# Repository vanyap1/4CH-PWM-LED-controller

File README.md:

# Потужний 4-канальний контролер освітлення

Контролер призначений для керування чотирма незалежними каналами освітлення за допомогою ШІМ. Підходить для амбіентного підсвічування та роботи з різними сенсорами присутності й освітленості.

## Основні можливості
- Керування **4 незалежними каналами**
- Регулювання яскравості через **ШІМ**
- Інтеграція з зовнішніми сенсорами:
  - Доплерівські сенсори присутності
  - PIR сенсори руху
  - Датчики освітленості
  - Інші сумісні датчики

## Система захисту
- **Температурний контроль** силових транзисторів
- Підтримка **зовнішнього NTC** біля навантаження
- **Захист по струму**
- **Контроль вхідної напруги** з блокуванням роботи в небезпечних діапазонах

## Технічні характеристики
- **Напруга живлення:** 12–26 В  
- **Споживання контролера:** ≤ 50 mA  
- **Максимальний струм комутації:**
  - до **12 А на канал**, або
  - до **12 А сумарно**

## Індикація роботи

### Зелений індикатор
- **Світиться** — нормальна робота  
- **Блимає** — перехідні процеси (зміна режиму, встановлення нового ШІМ)  
- **Вимкнений** — нештатна ситуація

### Червоний індикатор
- **Блимає** — відновлювані критичні стани  
  (критична напруга, перегрів, обмеження по струму, таймер блокування).  
  Виходи **вимкнені**  
- **Світиться** — фатальна помилка  
  (критичний перегрів, неможливість контролювати/відключити навантаження).  
  Скидання після перезапуску, якщо проблема не повторюється

## Програмування сценаріїв
Поведінку контролера, сценарії роботи та інтеграцію з сенсорами можна налаштовувати індивідуально під проєкт.

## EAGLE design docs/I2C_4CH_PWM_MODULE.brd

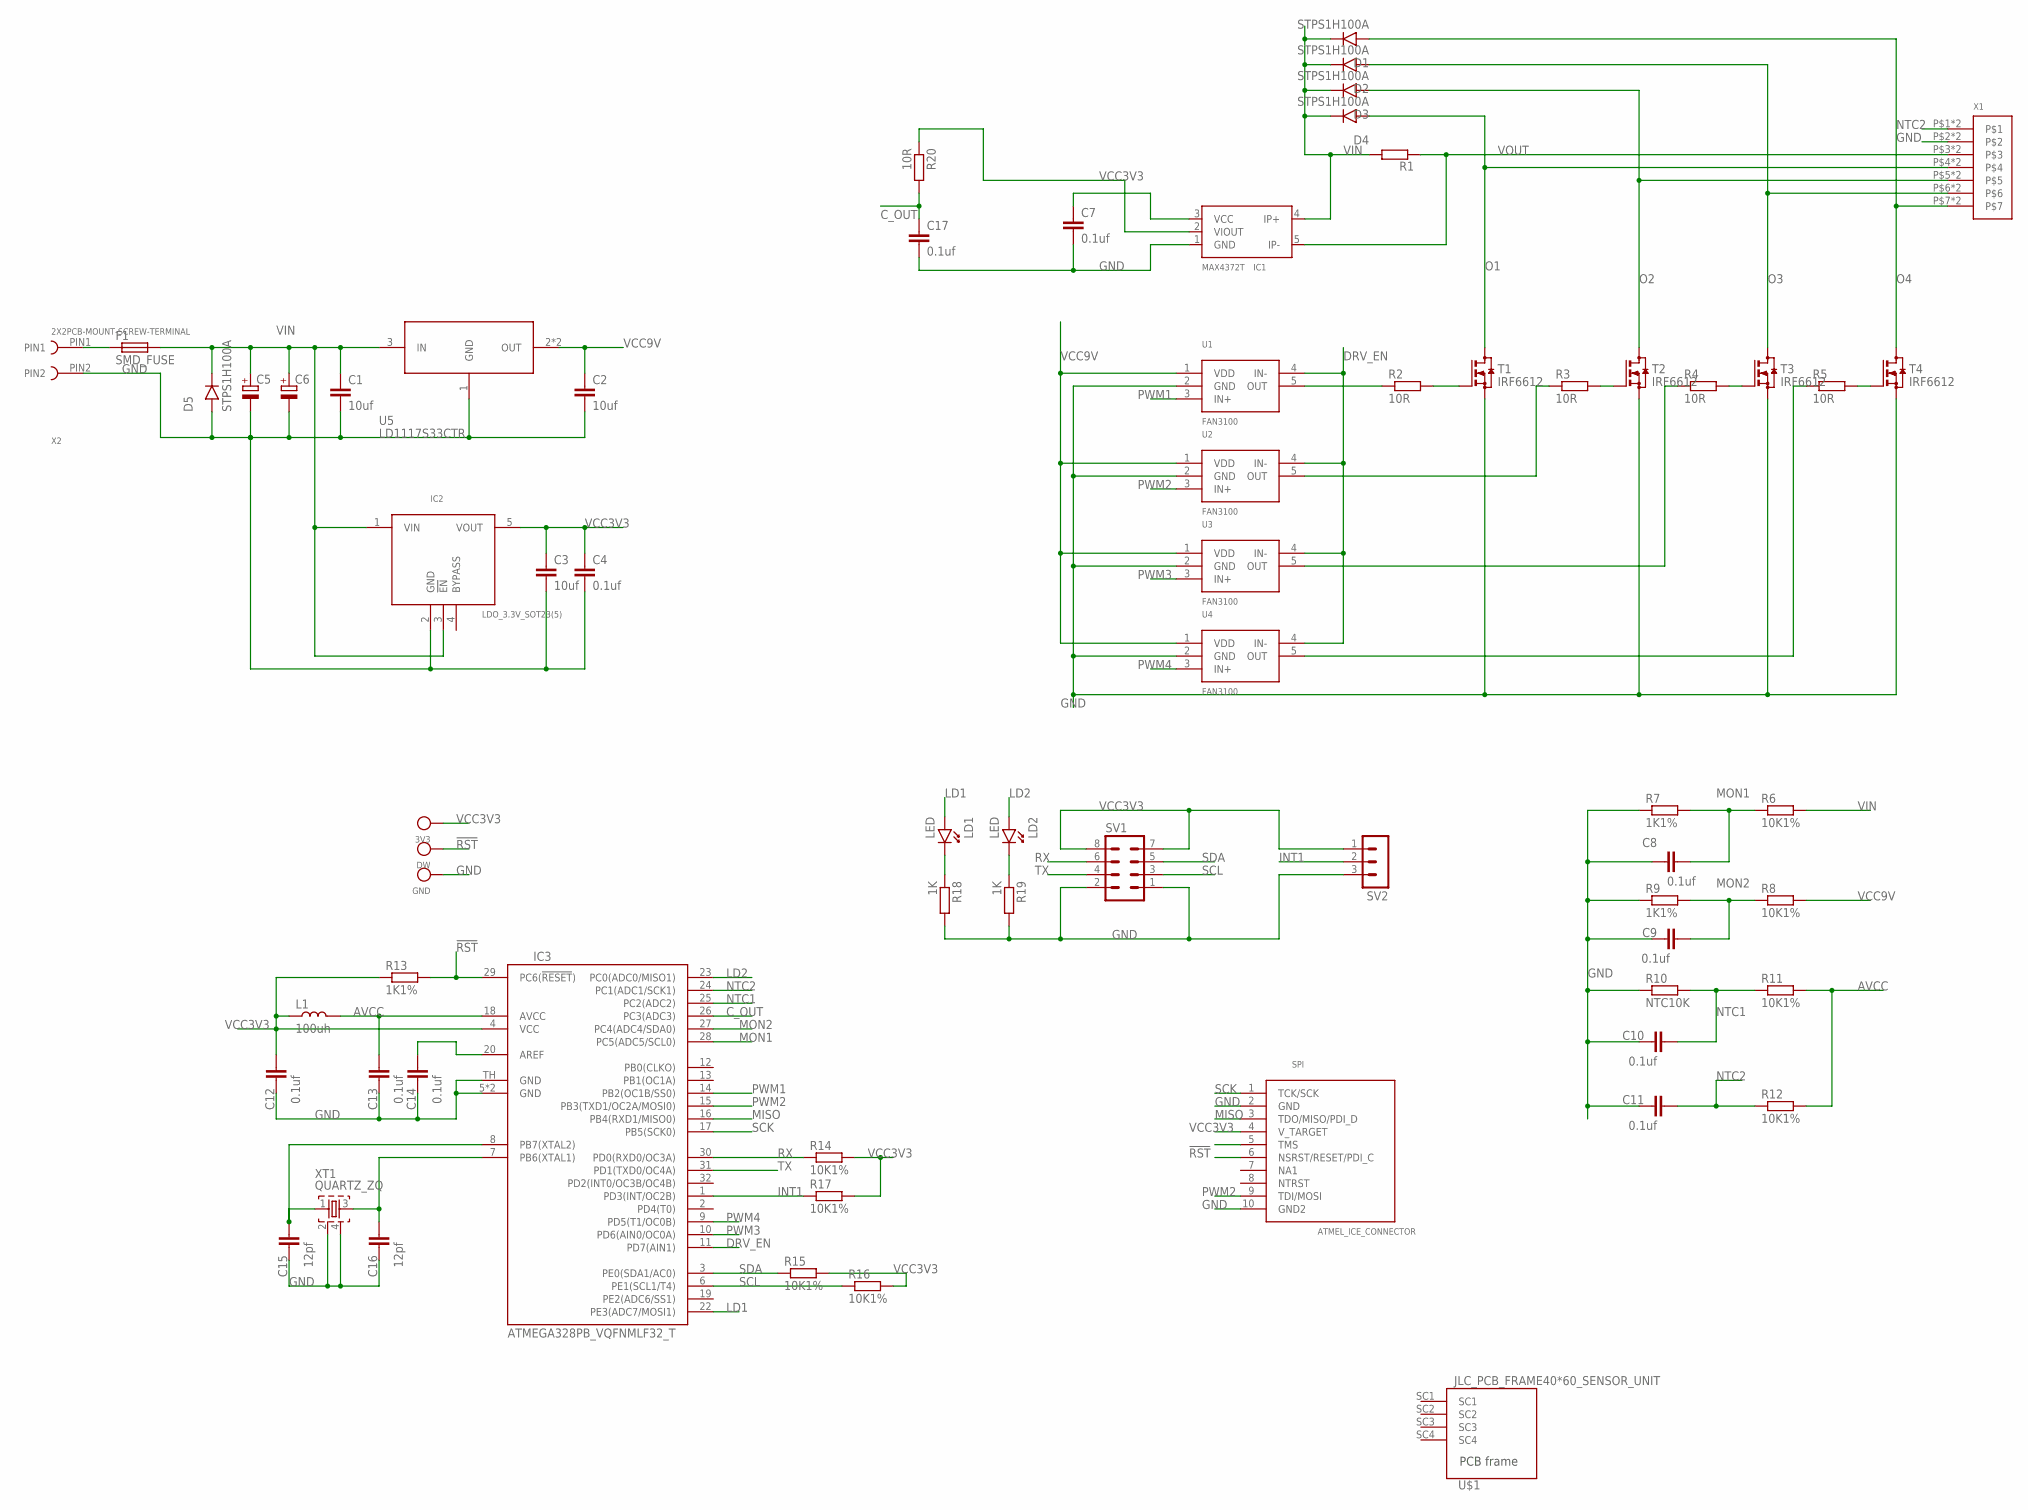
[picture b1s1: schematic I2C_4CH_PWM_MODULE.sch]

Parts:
3V3: TEST_POINT_D2MM; TP
C1, C2, C3: 10uf; 1206
C4, C7, C8, C9, C10, C11, C12, C13, C14, C17: 0.1uf; 0603
C5, C6: CPOL-EU153CLV-0605; 153CLV-0605
C15, C16: 12pf; 0603
D1, D2, D3, D4, D5: STPS1H100A; SMA403D
DW: TEST_POINT_D2MM; TP
F1: SMD_FUSE; SMD_2410_FUSE_NOK
GND: TEST_POINT_D2MM; TP
IC1: MAX4372T; SOT-23(5)
IC2: LDO_3.3V_SOT23(5); SOT-23(5)
IC3: ATMEGA328PB_VQFNMLF32_T; MLF32-TH
L1: 100uh; 0603
LD1, LD2: LED; 3MM_DIP_LED
R1: SMS-0
R2, R3, R4, R5, R20: 10R; 0603
R6, R8, R11, R12, R14, R15, R16, R17: 10K1%; 0603
R7, R9, R13: 1K1%; 0603
R10: NTC10K; 0603
R18, R19: 1K; 0603
SPI: ATMEL_ICE_CONNECTOR; MINI10P_SPI/JTAG/PDI
SV1: MA04-2
SV2: MA03-1
T1, T2, T3, T4: IRF6612; DIRECTFET_IRF6612
U1, U2, U3, U4: FAN3100; SOT-23(5)
U5: LD1117S33CTR; SOT223
U$1: JLC_PCB_FRAME40*60_SENSOR_UNIT; 40X60_SENSOR_UNIT
X1: WAGO250_X7; WAGO250_FP_7X
X2: 2X2PCB-MOUNT-SCREW-TERMINAL
XT1: QUARTZ_ZQ; QUARTZ_3X3MM

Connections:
!RST: DW.P$1, IC3.29 (PC6(!RESET!)), R13.2, SPI.6 (NSRST/RESET/PDI_C)
AVCC: C13.2, IC3.18 (AVCC), L1.2, R11.2, R12.2
C_OUT: C17.1, IC3.26 (PC3(ADC3)), R20.2
DRV_EN: IC3.11 (PD7(AIN1)), U1.4 (IN-), U2.4 (IN-), U3.4 (IN-), U4.4 (IN-)
GND: C1.2, C2.2, C3.2, C4.2, C5.-, C6.-, C7.2, C8.1, C9.1, C10.1, C11.1, C12.1, C13.1, C14.1, C15.1, C16.1, C17.2, D5.P$2 (A), GND.P$1, IC1.1 (GND), IC2.2 (GND), IC3.5 (GND), IC3.21 (GND), IC3.TH (GND), R7.1, R9.1, R10.1, R18.2, R19.2, SPI.2 (GND), SPI.10 (GND2), SV1.1, SV1.2, SV2.3, T1.S1 (S), T1.S2 (S), T2.S1 (S), T2.S2 (S), T3.S1 (S), T3.S2 (S), T4.S1 (S), T4.S2 (S), U1.2 (GND), U2.2 (GND), U3.2 (GND), U4.2 (GND), U5.1 (GND), X1.P$2, X1.U$2, X2.PIN2, XT1.2, XT1.4
INT1: IC3.1 (PD3(INT/OC2B)), R17.1, SV2.2
LD1: IC3.22 (PE3(ADC7/MOSI1)), LD1.A
LD2: IC3.23 (PC0(ADC0/MISO1)), LD2.A
MISO: IC3.16 (PB4(RXD1/MISO0)), SPI.3 (TDO/MISO/PDI_D)
MON1: C8.2, IC3.28 (PC5(ADC5/SCL0)), R6.1, R7.2
MON2: C9.2, IC3.27 (PC4(ADC4/SDA0)), R8.1, R9.2
unnamed: LD2.K, R19.1
unnamed: F1.P$1 (1), X2.PIN1
unnamed: C15.2, IC3.8 (PB7(XTAL2)), XT1.1
unnamed: C16.2, IC3.7 (PB6(XTAL1)), XT1.3
unnamed: C14.2, IC3.20 (AREF)
unnamed: LD1.K, R18.1
unnamed: IC1.2 (VIOUT), R20.1
unnamed: R2.2, T1.G
unnamed: R2.1, U1.5 (OUT)
unnamed: R3.1, U2.5 (OUT)
unnamed: R3.2, T2.G
unnamed: R4.1, U3.5 (OUT)
unnamed: R4.2, T3.G
unnamed: R5.1, U4.5 (OUT)
unnamed: R5.2, T4.G
NTC1: C10.2, IC3.25 (PC2(ADC2)), R10.2, R11.1
NTC2: C11.2, IC3.24 (PC1(ADC1/SCK1)), R12.1, X1.P$1, X1.U$1
O1: D4.P$2 (A), T1.D1 (D), T1.D2 (D), X1.P$4, X1.U$4
O2: D3.P$2 (A), T2.D1 (D), T2.D2 (D), X1.P$5, X1.U$5
O3: D2.P$2 (A), T3.D1 (D), T3.D2 (D), X1.P$6, X1.U$6
O4: D1.P$2 (A), T4.D1 (D), T4.D2 (D), X1.P$7, X1.U$7
PWM1: IC3.14 (PB2(OC1B/SS0)), U1.3 (IN+)
PWM2: IC3.15 (PB3(TXD1/OC2A/MOSI0)), SPI.9 (TDI/MOSI), U2.3 (IN+)
PWM3: IC3.10 (PD6(AIN0/OC0A)), U3.3 (IN+)
PWM4: IC3.9 (PD5(T1/OC0B)), U4.3 (IN+)
RX: IC3.30 (PD0(RXD0/OC3A)), R14.1, SV1.6
SCK: IC3.17 (PB5(SCK0)), SPI.1 (TCK/SCK)
SCL: IC3.6 (PE1(SCL1/T4)), R16.1, SV1.3
SDA: IC3.3 (PE0(SDA1/AC0)), R15.1, SV1.5
TX: IC3.31 (PD1(TXD0/OC4A)), SV1.4
VCC3V3: 3V3.P$1, C3.1, C4.1, C7.1, C12.2, IC1.3 (VCC), IC2.5 (VOUT), IC3.4 (VCC), L1.1, R13.1, R14.2, R15.2, R16.2, R17.2, SPI.4 (V_TARGET), SV1.7, SV1.8, SV2.1
VCC9V: C2.1, R8.2, U1.1 (VDD), U2.1 (VDD), U3.1 (VDD), U4.1 (VDD), U5.2 (OUT), U5.4 (OUT)
VIN: C1.1, C5.+, C6.+, D1.P$1 (C), D2.P$1 (C), D3.P$1 (C), D4.P$1 (C), D5.P$1 (C), F1.P$2 (2), IC1.4 (IP+), IC2.1 (VIN), IC2.3 (!EN!), R1.1, R6.2, U5.3 (IN)
VOUT: IC1.5 (IP-), R1.2, X1.P$3, X1.U$3

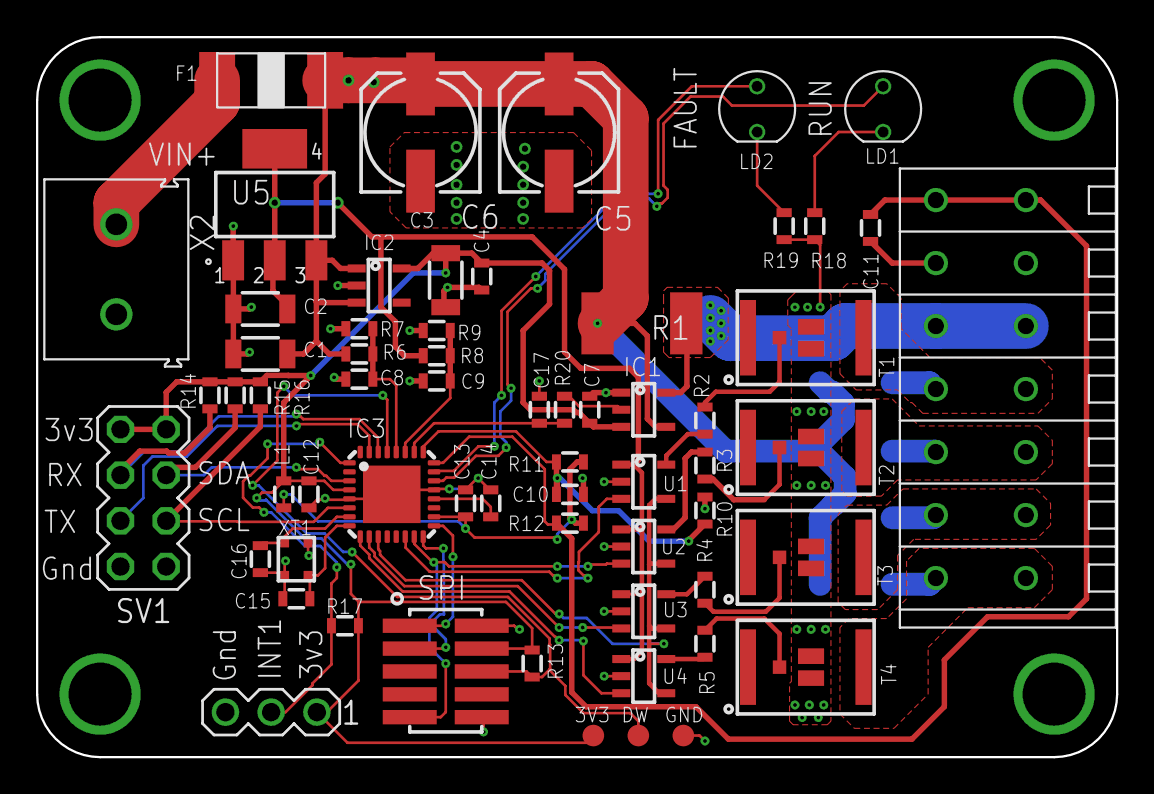
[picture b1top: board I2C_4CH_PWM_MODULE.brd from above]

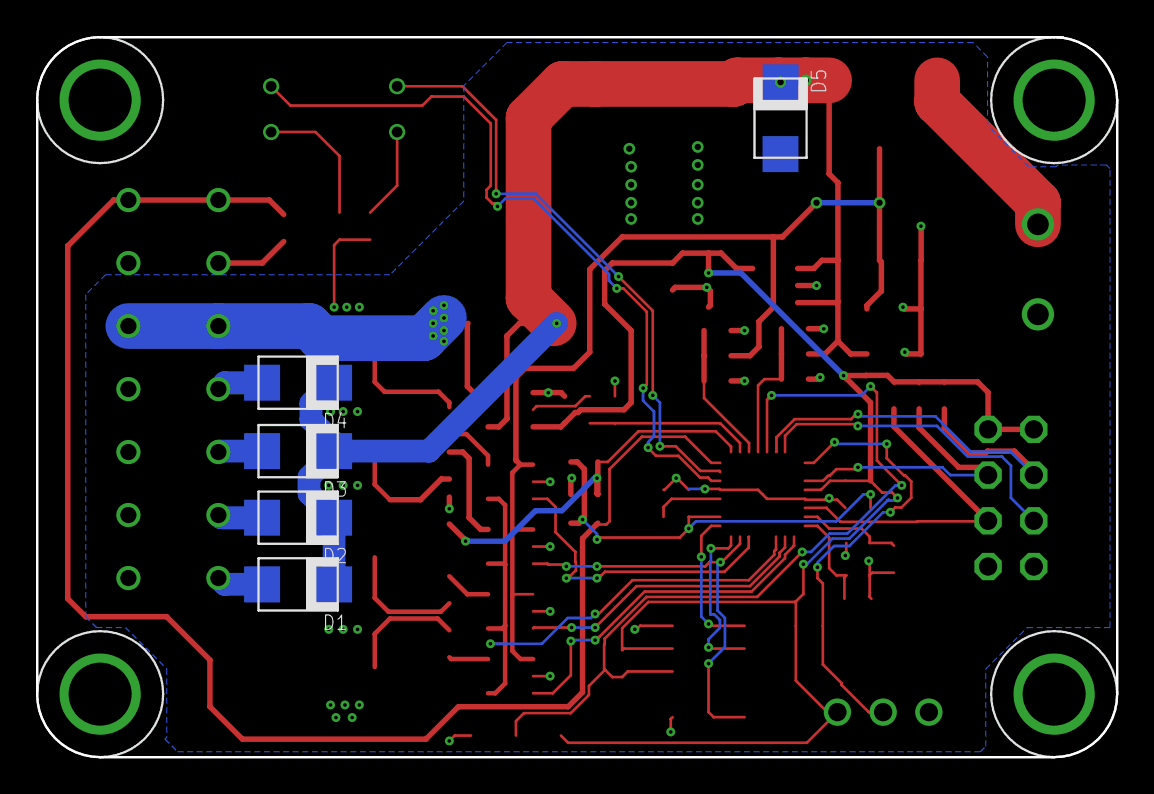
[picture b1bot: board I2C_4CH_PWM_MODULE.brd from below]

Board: 2 copper layers, 60.0 x 40.0 mm, 68 parts (6 on the bottom side), 45 nets.

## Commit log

2023-12-14 added working code and docs
2025-12-01 Add README with product details and features
